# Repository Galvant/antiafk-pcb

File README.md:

antiAFK PCB
===========

This repository contains the KiCAD PCB project files for the antiAFK.

The associated firmware project can be found on GitHub at www.github.com/Galvant/antiafk_firmware

Pre-assembled boards will be available shortly at [Galvant Industries](www.galvant.ca)

Project Details
---------------

Please see the README.md file [in the firmware repository](https://github.com/Galvant/antiAFK_firmware)
to learn more about this project.

License
-------

This work is released under the Creative Commons Attribution-Sharealike 3.0 license. 
See http://creativecommons.org/licenses/by-sa/3.0/ or the included license/LICENSE.TXT file 
for more information.

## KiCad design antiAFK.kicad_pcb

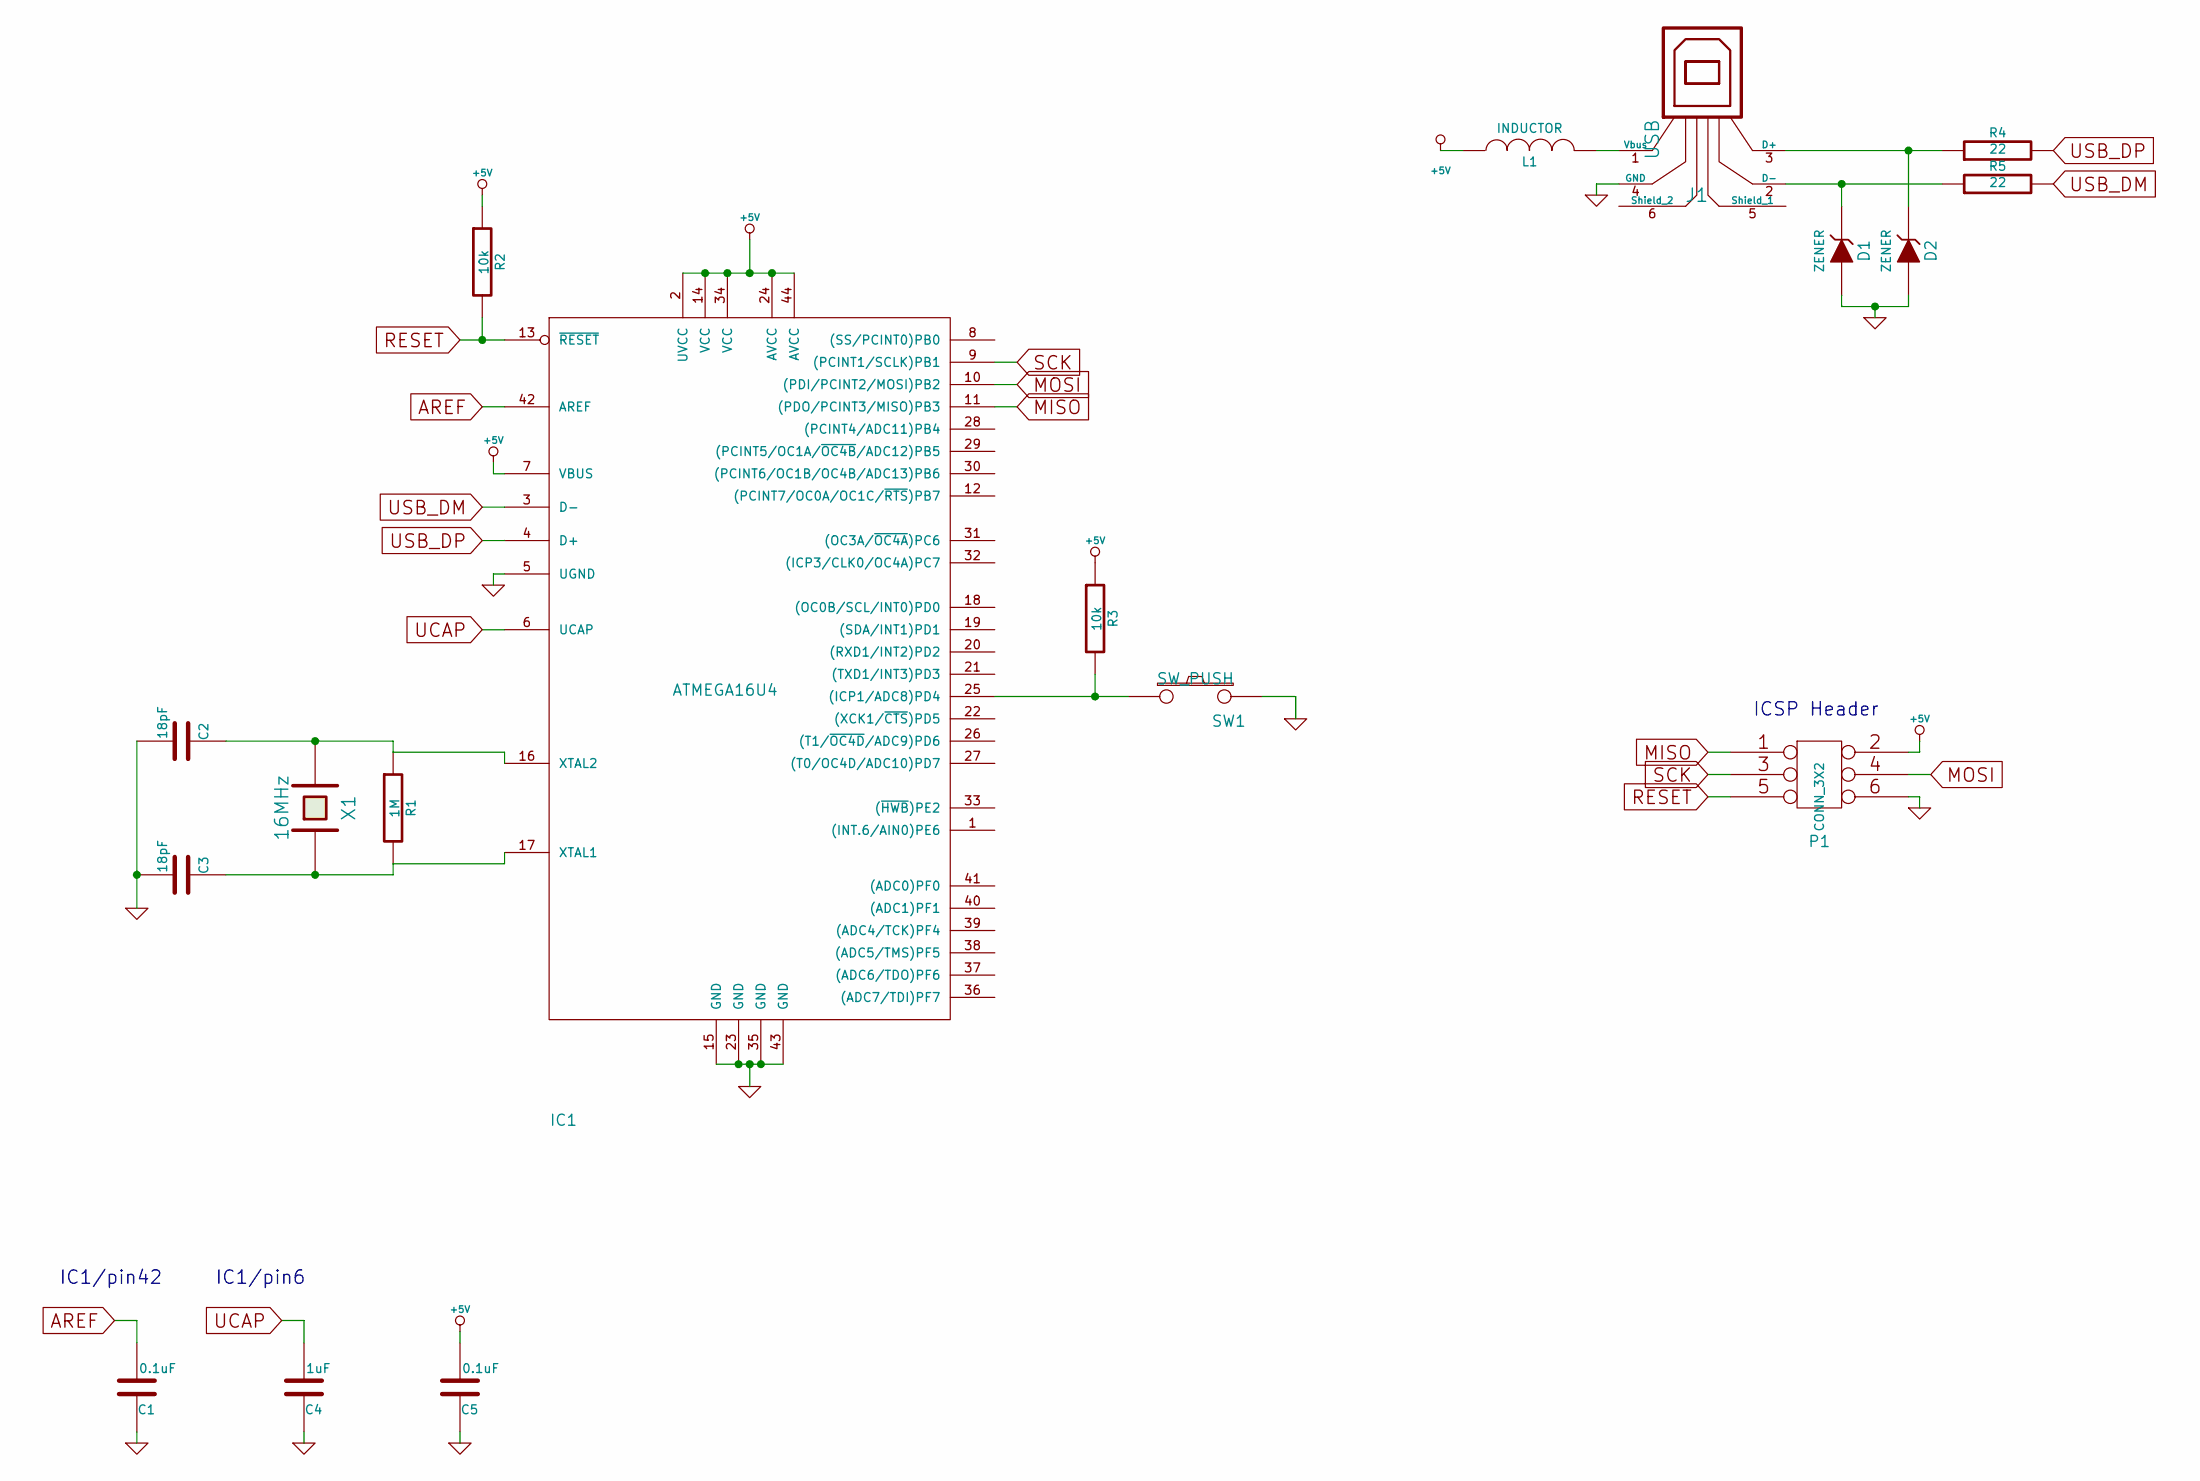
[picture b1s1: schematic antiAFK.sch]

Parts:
C1, C5: 0.1uF
C2, C3: 18pF
C4: 1uF
D1, D2: ZENER
IC1: ATMEGA16U4; TQFP44
J1: USB
L1: INDUCTOR
P1: CONN_3X2
R1: 1M
R2, R3: 10k
R4, R5: 22
SW1: SW_PUSH
X1: 16MHz

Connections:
+5V: C5.1, IC1.2 (UVCC), IC1.7 (VBUS), IC1.14 (VCC), IC1.24 (AVCC), IC1.34 (VCC), IC1.44 (AVCC), L1.1, P1.2, R2.1, R3.1
AREF: C1.1, IC1.42 (AREF)
GND: C1.2, C2.1, C3.1, C4.2, C5.2, D1.1 (A), D2.1 (A), IC1.5 (UGND), IC1.15 (GND), IC1.23 (GND), IC1.35 (GND), IC1.43 (GND), J1.4 (GND), P1.6, SW1.2, X1.3
MISO: IC1.11 ((PDO/PCINT3/MISO)PB3), P1.1
MOSI: IC1.10 ((PDI/PCINT2/MOSI)PB2), P1.4
unnamed: IC1.25 ((ICP1/ADC8)PD4), R3.2, SW1.1
unnamed: C2.2, IC1.16 (XTAL2), R1.1, X1.2
unnamed: J1.1 (Vbus), L1.2
unnamed: D1.2 (K), J1.2 (D-), R5.1
unnamed: D2.2 (K), J1.3 (D+), R4.1
unnamed: C3.2, IC1.17 (XTAL1), R1.2, X1.1
RESET: IC1.13 (~RESET), P1.5, R2.2
SCK: IC1.9 ((PCINT1/SCLK)PB1), P1.3
UCAP: C4.1, IC1.6 (UCAP)
USB_DM: IC1.3 (D-), R5.2
USB_DP: IC1.4 (D+), R4.2

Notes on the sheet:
IC1/pin42
IC1/pin6
ICSP Header

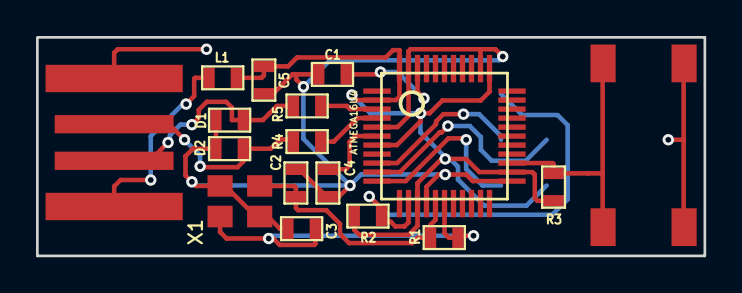
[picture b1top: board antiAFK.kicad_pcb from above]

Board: 2 copper layers, 37.1 x 12.1 mm, 18 parts (1 on the bottom side), 16 nets.

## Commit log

2013-09-29 Initial project commit
2014-01-23 Moved gerbers, removed backup files
2014-01-23 Update author years
